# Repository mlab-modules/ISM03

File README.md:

# ISM03 - Si4463-based transceiver with SPI interface

The ISM03 is a high-performance wireless transceiver designed for long-distance data transmission. The module is based on the [Si4463 chip](https://www.silabs.com/wireless/proprietary/ezradiopro-sub-ghz-ics/device.si4463?tab=specs) from Silicon Labs. It has a wide frequency range and output power, it is ideal for applications that require robust and reliable wireless communication.

ISM03 can operate on the open 433 or 868 MHz frequencies, which are popular in many applications.

## Parameters

- Based on the Si4463 chip
- Chip frequency range: 142 to 1050 MHz, with the ability to operate on the open 433 or 868 MHz frequencies
- Chip output power: -20 to 20 dBm
- The Si4463 chip includes a programmable block capable of controlling radio settings and supports the SPI interface
- Power supply: 5-12V with integrated 3.3V stabilizer
- Communication: SPI, GPIO
- Accessible GPIO signals directly from the transceiver
- Status indication: Two LEDs controlled from the Si chip
- Antenna connectors: MCX for RX and TX antennas. For bidirectional communication with a single antenna, connecting the [RFSWITCH module](www.mlab.cz/module/RFSWITCH01/) is recommended, which serves as an RF switch and enables MIMO 2x2 support. ISM03 can control the RFSWITCH module through GPIO pins

## Possible Applications

The MLAB ISM03 module with the Si4463 transceiver is suitable for various applications. It can be used in areas such as:

- **Remote Control**: The module can be used for wireless control of various devices, such as drones, RC cars, or home automation.
- **Data Links**: With a suitable firmware, the module can function as a [SiK data communication link](https://ardupilot.org/copter/docs/common-sik-telemetry-radio.html), which can transmit [MAVLink packets](https://mavlink.io/en/). MAVLink is a protocol designed for communication with unmanned vehicles and is supported by the most widespread autopilots Ardupilot and PX4. This is ideal for applications that require wireless data transmission.
- **Wireless Sensor Networks**: The module can be used to create wireless sensor networks in IoT applications.

> Based on this module, the company [ThunderFly](https://www.thunderfly.cz) has developed a module optimized for use on drones, which combines this ISM03 module, RFSWITCH01A, and additional RF filters and LNA. That could be integrated directly to the autopilot PCB to save weight.

## Links to Related Resources

- [Silicon Labs Si4463 Product Page](https://www.silabs.com/wireless/proprietary/ezradiopro-sub-ghz-ics/device.si4463?tab=specs)
- [Si4463 Datasheet](https://www.silabs.com/documents/public/data-sheets/Si4464-63-61-60.pdf)
- [MavLink Protocol](https://mavlink.io/en/)
- [SiK Radio](https://ardupilot.org/copter/docs/common-sik-telemetry-radio.html)
- [EZRADioPRO Family](https://www.silabs.com/wireless/proprietary/ezradiopro-sub-ghz-ics)
- [TFSIK01 Module by ThunderFly](https://github.com/ThunderFly-aerospace/TFSIK01/)

---

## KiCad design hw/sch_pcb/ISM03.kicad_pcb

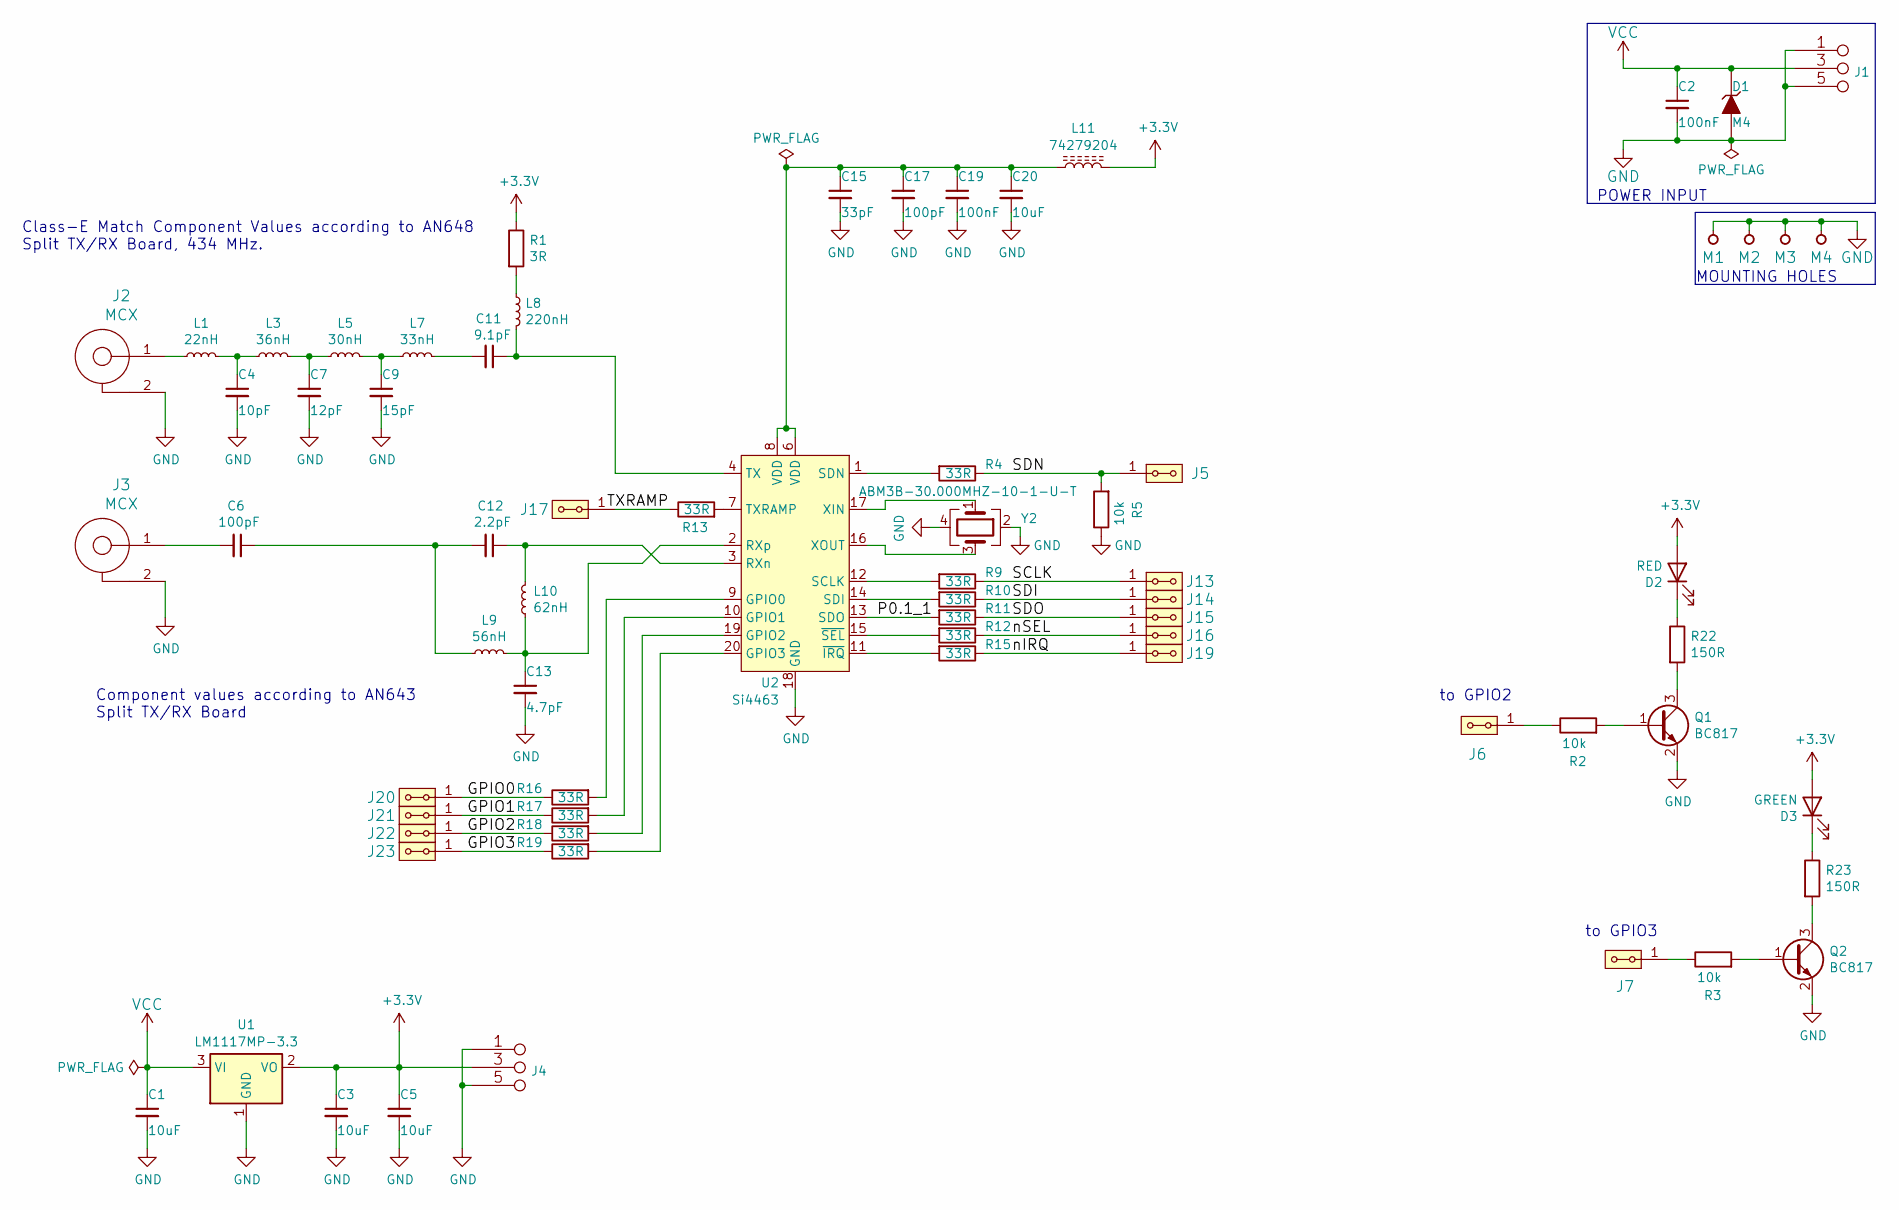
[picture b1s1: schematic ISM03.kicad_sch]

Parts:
C1, C3, C5, C20: 10uF; C_0805_2012Metric
C2, C19: 100nF; C_0805_2012Metric
C4: 10pF; C_0805_2012Metric
C6, C17: 100pF; C_0805_2012Metric
C7: 12pF; C_0805_2012Metric
C9: 15pF; C_0805_2012Metric
C11: 9.1pF; C_0805_2012Metric
C12: 2.2pF; C_0805_2012Metric
C13: 4.7pF; C_0805_2012Metric
C15: 33pF; C_0805_2012Metric
D1: M4; D_SMA
D2: RED; LED_1206
D3: GREEN; LED_1206
J1, J4: JUMP_3X2; Straight_2x03
J2, J3: MCX; SMA6251A13G50
J5, J6, J7, J13, J14, J15, J16, J17, J19, J20, J21, J22, J23: HEADER_2x01_PARALLEL; Straight_2x01
L1: 22nH; R_0805_2012Metric
L3: 36nH; L_0805_2012Metric
L5: 30nH; L_0805_2012Metric
L7: 33nH; L_0805_2012Metric
L8: 220nH; L_0805_2012Metric
L9: 56nH; L_0805_2012Metric
L10: 62nH; L_0805_2012Metric
L11: 74279204; L_0805_2012Metric
M1, M2, M3, M4: HOLE; MountingHole_3mm
Q1, Q2: BC817; SOT-23
R1: 3R; R_0805_2012Metric
R2, R3, R5: 10k; R_0805_2012Metric
R4, R9, R10, R11, R12, R13, R15, R16, R17, R18, R19: 33R; R_0805_2012Metric
R22, R23: 150R; R_0805_2012Metric
U1: LM1117MP-3.3; SOT-223-3_TabPin2
U2: Si4463; QFN-20-1EP_4x4mm_P0.5mm_EP2.6x2.6mm_ThermalVias
Y2: ABM3B-30.000MHZ-10-1-U-T; Crystal_SMD_Abracon_ABM3B-4Pin_5.0x3.2mm

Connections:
+3.3V: C3.1, C5.1, D2.2 (A), D3.2 (A), J4.3 (4), J4.4, L11.2, R1.1, U1.2 (VO)
/GPIO0: J20.1, J20.2, R16.1
/GPIO1: J21.1, J21.2, R17.1
/GPIO2: J22.1, J22.2, R18.1
/GPIO3: J23.1, J23.2, R19.1
/P0.1_1: R11.2, U2.13 (SDO)
/SCLK: J13.1, J13.2, R9.1
/SDI: J14.1, J14.2, R10.1
/SDN: J5.1, J5.2, R4.1, R5.2
/SDO: J15.1, J15.2, R11.1
/TXRAMP: J17.1, J17.2, R13.1
/nIRQ: J19.1, J19.2, R15.1
/nSEL: J16.1, J16.2, R12.1
GND: C1.2, C2.2, C3.2, C4.2, C5.2, C7.2, C9.2, C13.2, C15.2, C17.2, C19.2, C20.2, D1.2 (A), J1.1 (2), J1.2, J1.5 (6), J1.6, J2.2, J3.2, J4.1 (2), J4.2, J4.5 (6), J4.6, M1.1, M2.1, M3.1, M4.1, Q1.2 (E), Q2.2 (E), R5.1, U1.1 (GND), U2.18 (GND), U2.21 (GND), Y2.2, Y2.4
unnamed: C4.1, L1.2, L3.1
unnamed: C6.2, J3.1
unnamed: C7.1, L3.2, L5.1
unnamed: C9.1, L5.2, L7.1
unnamed: C11.2, L7.2
unnamed: C6.1, C12.2, L9.1
unnamed: C15.1, C17.1, C19.1, C20.1, L11.1, U2.6 (VDD), U2.8 (VDD)
unnamed: D2.1 (K), R22.1
unnamed: D3.1 (K), R23.1
unnamed: J2.1, L1.1
unnamed: J6.1, J6.2, R2.1
unnamed: J7.1, J7.2, R3.1
unnamed: L8.1, R1.2
unnamed: Q1.1 (B), R2.2
unnamed: Q1.3 (C), R22.2
unnamed: Q2.1 (B), R3.2
unnamed: Q2.3 (C), R23.2
unnamed: R16.2, U2.9 (GPIO0)
unnamed: R17.2, U2.10 (GPIO1)
unnamed: R18.2, U2.19 (GPIO2)
unnamed: R19.2, U2.20 (GPIO3)
unnamed: C12.1, L10.2, U2.3 (RXn)
unnamed: C13.1, L9.2, L10.1, U2.2 (RXp)
unnamed: R9.2, U2.12 (SCLK)
unnamed: R10.2, U2.14 (SDI)
unnamed: R4.2, U2.1 (SDN)
unnamed: C11.1, L8.2, U2.4 (TX)
unnamed: R13.2, U2.7 (TXRAMP)
unnamed: U2.17 (XIN), Y2.1
unnamed: U2.16 (XOUT), Y2.3
unnamed: R15.2, U2.11 (~IRQ)
unnamed: R12.2, U2.15 (~SEL)
VCC: C1.1, C2.1, D1.1 (K), J1.3 (4), J1.4, U1.3 (VI)

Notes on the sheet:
POWER INPUT
Component values according to AN643 Split TX/RX Board
to GPIO3
to GPIO2
Class-E Match Component Values according to AN648 Split TX/RX Board, 434 MHz.
MOUNTING HOLES

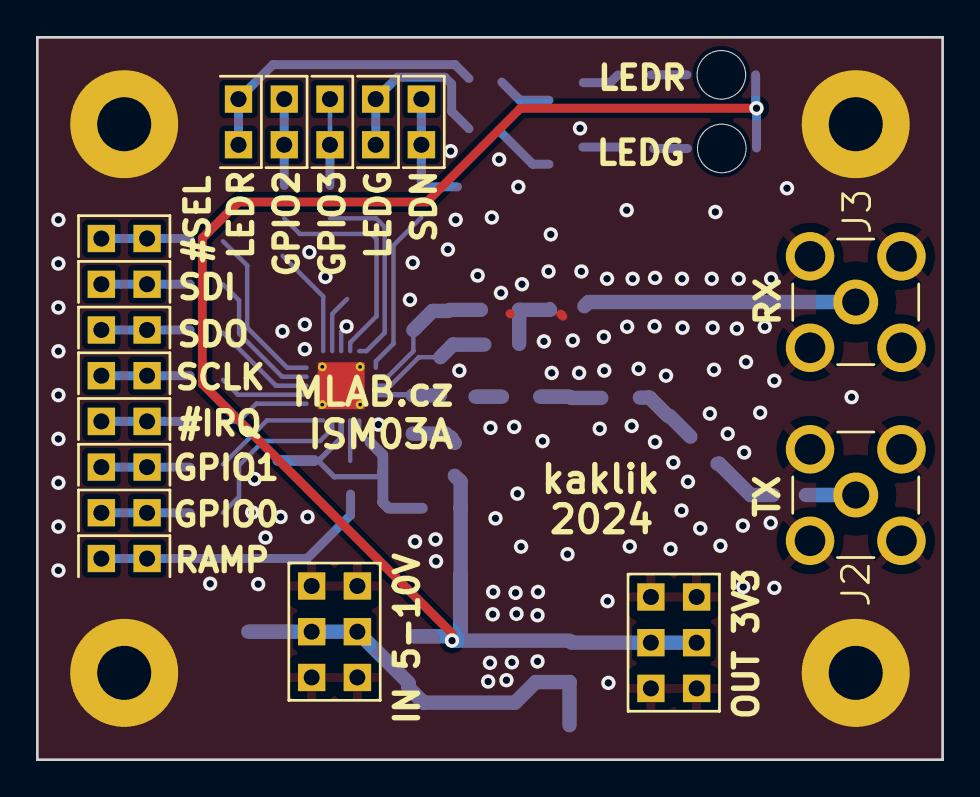
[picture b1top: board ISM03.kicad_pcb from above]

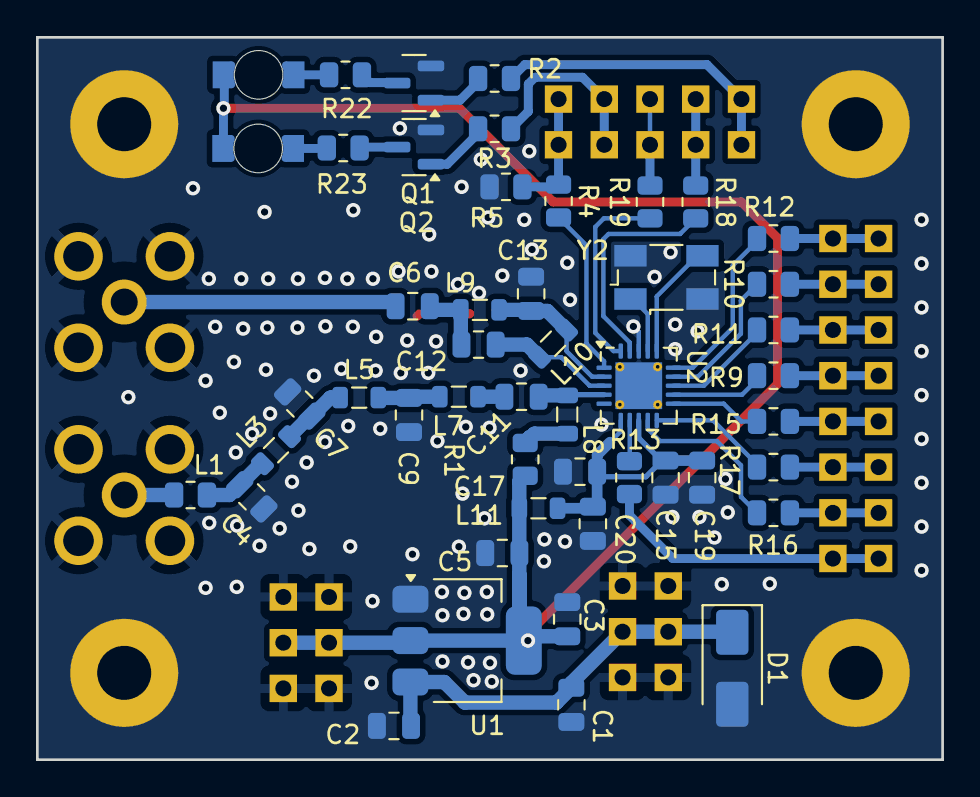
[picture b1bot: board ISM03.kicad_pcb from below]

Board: 2 copper layers, 50.3 x 40.1 mm, 69 parts (48 on the bottom side), 47 nets.

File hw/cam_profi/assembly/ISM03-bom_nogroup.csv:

Component,Description,Part,References,Value,Footprint,Quantity Per PCB,Datasheet,ust_id
1,"Unpolarized capacitor, small symbol",C_Small,C12,2.2pF,C_0805_2012Metric,1,~,5c70984712875079b91f8b27
2,"Unpolarized capacitor, small symbol",C_Small,C13,4.7pF,C_0805_2012Metric,1,~,5c70984712875079b91f8b2c
3,"Unpolarized capacitor, small symbol",C_Small,C11,9.1pF,C_0805_2012Metric,1,~,611b60e71287500165a9732d
4,"Unpolarized capacitor, small symbol",C_Small,C4,10pF,C_0805_2012Metric,1,~,5c70984712875079b91f8b30
5,"Unpolarized capacitor, small symbol",C_Small,C7,12pF,C_0805_2012Metric,1,~,5c70984712875079b91f8b31
6,"Unpolarized capacitor, small symbol",C_Small,C9,15pF,C_0805_2012Metric,1,~,5c70984712875079b91f8b32
7,"Unpolarized capacitor, small symbol",C_Small,C15,33pF,C_0805_2012Metric,1,~,5c70984712875079b91f8b37
8,"Unpolarized capacitor, small symbol",C_Small,C6C17,100pF,C_0805_2012Metric,2,~,5c70984712875079b91f8b3b
9,"Unpolarized capacitor, small symbol",C_Small,C2C19,100nF,C_0805_2012Metric,2,~,5c70984712875079b91f8b4c
10,"Unpolarized capacitor, small symbol",C_Small,C1C3C5C20,10uF,C_0805_2012Metric,4,~,5c70984812875079b91f8bbd
11,Light emitting diode,LED,D3,GREEN,LED_1206,1,~,5c70984412875079b91f8895
12,,D_ZENER,D1,M4,D_SMA,1,,5c70984512875079b91f88ac
13,Light emitting diode,LED,D2,RED,LED_1206,1,~,5c70984412875079b91f8896
14,"2x01 2.54 mm pitch header, 2 pins next to each other are connected",HEADER_2x01_PARALLEL,J5J6J7J13J14J15J16J17J19J20J21J22J23,HEADER_2x01_PARALLEL,Straight_2x01,13,,
15,MLAB modified doubled pinheader connector,JUMP_3X2,J1J4,JUMP_3X2,Straight_2x03,2,,
16,,SMA,J2J3,MCX,SMA6251A13G50,2,,5c70984412875079b91f87ac
17,"Inductor, small symbol",L_Small,L1,22nH,R_0805_2012Metric,1,~,60be80ed1287500165e6c3bb
18,"Inductor, small symbol",L_Small,L5,30nH,L_0805_2012Metric,1,~,611b69d31287500165a9742b
19,"Inductor, small symbol",L_Small,L7,33nH,L_0805_2012Metric,1,~,5c70984412875079b91f8808
20,"Inductor, small symbol",L_Small,L3,36nH,L_0805_2012Metric,1,~,66a10bc36fdfe6f54e2ebbf8
21,"Inductor, small symbol",L_Small,L9,56nH,L_0805_2012Metric,1,~,5c70984812875079b91f8ba4
22,"Inductor, small symbol",L_Small,L10,62nH,L_0805_2012Metric,1,~,66a127196fdfe6f54e2ebd35
23,"Inductor, small symbol",L_Small,L8,220nH,L_0805_2012Metric,1,~,5c70984412875079b91f880d
24,Inductor with ferrite core,L_Ferrite,L11,74279204,L_0805_2012Metric,1,~,6016f01e1287504e4aa85f2a
25,"NPN transistor, base/emitter/collector",Q_NPN_BEC,Q1Q2,BC817,SOT-23,2,~,5c70984712875079b91f8aec
26,Resistor,R,R1,3R,R_0805_2012Metric,1,~,60d57f1a1287500165f858ae
27,Resistor,R,R4R9R10R11R12R13R15R16R17R18R19,33R,R_0805_2012Metric,11,~,5c70984512875079b91f8970
28,Resistor,R,R22R23,150R,R_0805_2012Metric,2,~,5c70984512875079b91f897a
29,Resistor,R,R2R3R5,10k,R_0805_2012Metric,3,~,5c70984612875079b91f899f
30,"800mA Low-Dropout Linear Regulator, 3.3V fixed output, SOT-223",LM1117MP-3.3,U1,LM1117MP-3.3,SOT-223-3_TabPin2,1,http://www.ti.com/lit/ds/symlink/lm1117.pdf,5c70984712875079b91f8af9
31,"High-Performance, Low-Current Sub-GHz Transceiver, +20dBm, Major bands 142-1050 MHz, QFN-20",Si4463,U2,Si4463,QFN-20-1EP_4x4mm_P0.5mm_EP2.6x2.6mm_ThermalVias,1,https://www.silabs.com/documents/public/data-sheets/Si4464-6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,5c70984612875079b91f8a0a
32,"Four pin crystal, GND on pins 2 and 4",Crystal_GND24,Y2,ABM3B-30.000MHZ-10-1-U-T,Crystal_SMD_Abracon_ABM3B-4Pin_5.0x3.2mm,1,~,5c70984712875079b91f8ba1

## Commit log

2024-07-12 Update workflow files
2024-07-12 Update metadata files
2024-07-12 Symplified transceiver WiP.
2024-07-12 Update actions products
2024-07-13 Update documentation PCB WiP.
2024-07-13 Backup work before switching to KiCADv8
2024-07-13 Convert project to KiCAD 8.
2024-07-14 Fix assets submodule branch.
2024-07-14 Routing WiP.
2024-07-14 Roughtly routet PCB.
2024-07-15 Update README.md
    Fix the link to the image.
2024-07-15 Fix silksceen.
2024-07-15 Fix branch.
2024-07-23 Cleanup layout. Correcly move References and texts.
2024-07-23 Improve Layout, silkscreen Update footprint from libraries.
2024-07-24 Removing old files.
2024-07-24 Update components identification.
2024-07-24 Fix inductor type.
2024-07-26 Fix fab layer.
2026-01-18 Update module status.
